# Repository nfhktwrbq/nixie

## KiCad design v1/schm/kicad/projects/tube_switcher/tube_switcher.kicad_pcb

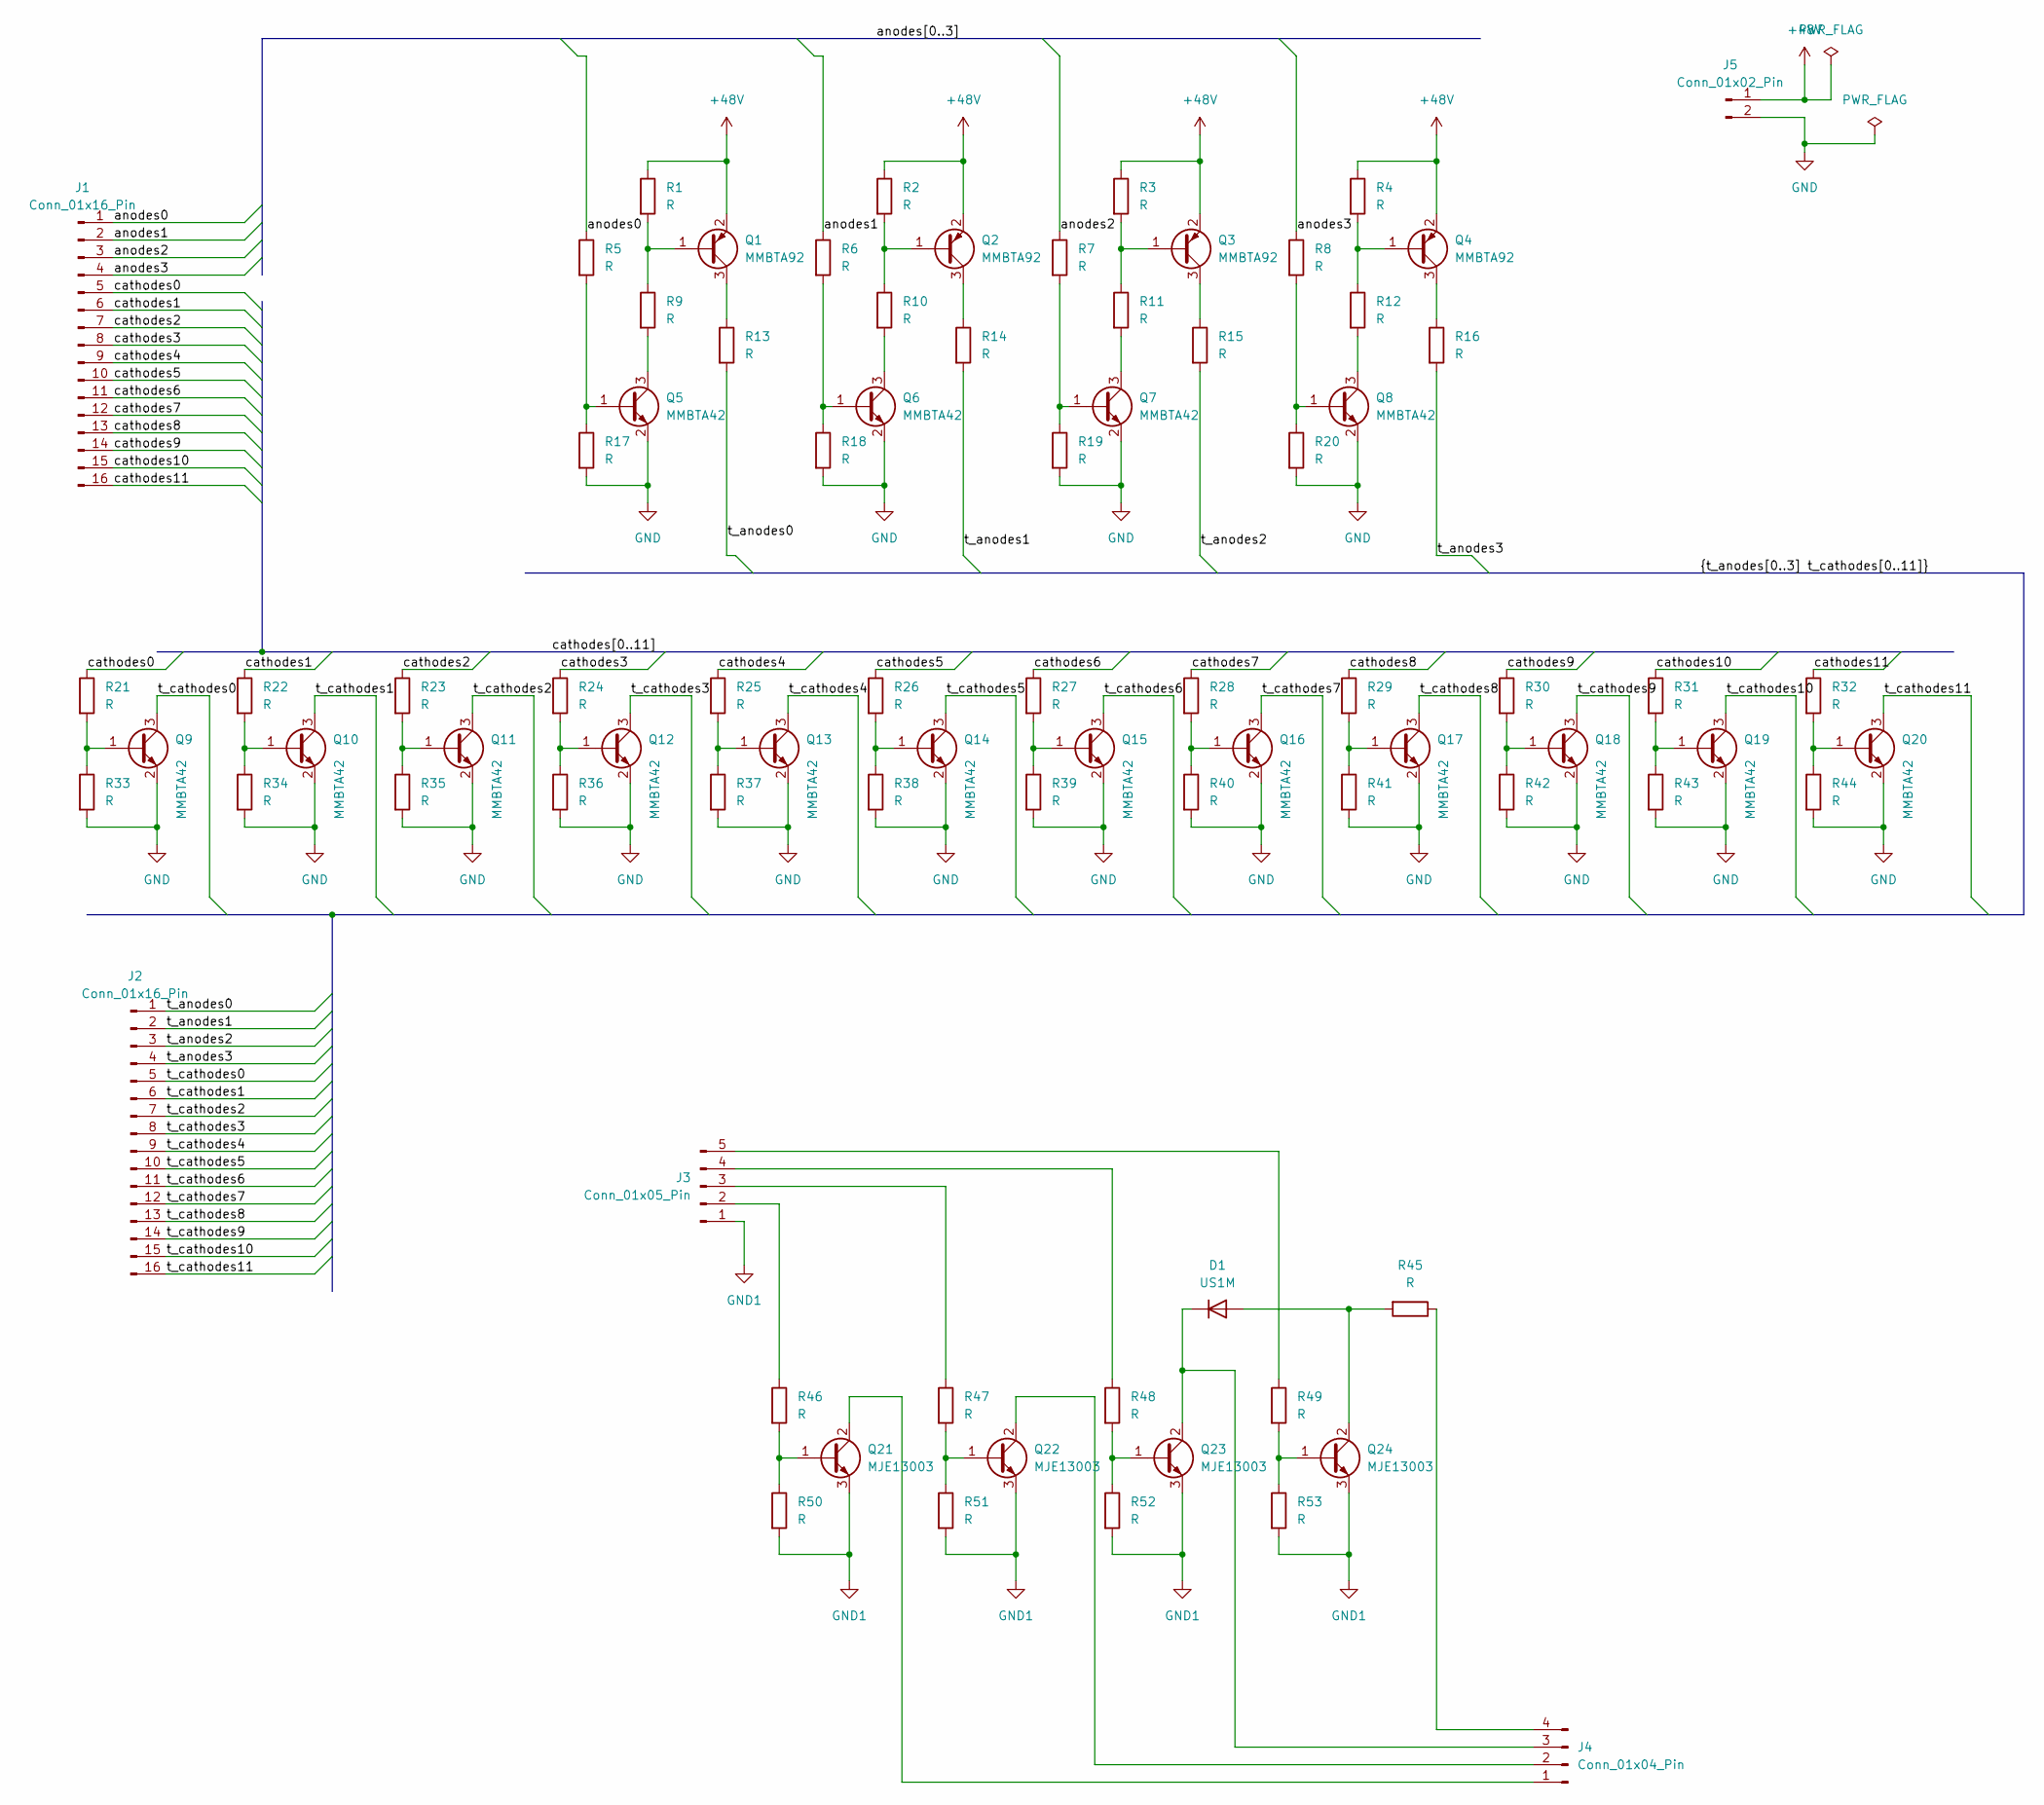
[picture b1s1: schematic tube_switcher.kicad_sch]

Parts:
D1: US1M; D_SMA
J1, J2: Conn_01x16_Pin; JST_XH_B16B-XH-A_1x16_P2.50mm_Vertical
J3: Conn_01x05_Pin; JST_XH_B5B-XH-A_1x05_P2.50mm_Vertical
J4: Conn_01x04_Pin; JST_XH_B4B-XH-A_1x04_P2.50mm_Vertical
J5: Conn_01x02_Pin; JST_XH_B2B-XH-A_1x02_P2.50mm_Vertical
Q1, Q2, Q3, Q4: MMBTA92; SOT-23
Q5, Q6, Q7, Q8, Q9, Q10, Q11, Q12, Q13, Q14, Q15, Q16, Q17, Q18, Q19, Q20: MMBTA42; SOT-23
Q21, Q22, Q23, Q24: MJE13003; TO-92_Inline_Wide
R1, R2, R3, R4, R9, R10, R11, R12: R; R_0805_2012Metric_Pad1.20x1.40mm_HandSolder
R5, R6, R7, R8, R17, R18, R19, R20, R21, R22, R23, R24, R25, R26, R27, R28, R29, R30, R31, R32, R33, R34, R35, R36, R37, R38, R39, R40, R41, R42, R43, R44, R46, R47, R48, R49, R50, R51, R52, R53: R; R_0402_1005Metric_Pad0.72x0.64mm_HandSolder
R13, R14, R15, R16, R45: R; R_1206_3216Metric_Pad1.30x1.75mm_HandSolder

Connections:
+48V: J5.1, Q1.2 (E), Q2.2 (E), Q3.2 (E), Q4.2 (E), R1.1, R2.1, R3.1, R4.1
/anodes0: J1.1, R5.1
/anodes1: J1.2, R6.1
/anodes2: J1.3, R7.1
/anodes3: J1.4, R8.1
/cathodes0: J1.5, R21.1
/cathodes1: J1.6, R22.1
/cathodes2: J1.7, R23.1
/cathodes3: J1.8, R24.1
/cathodes4: J1.9, R25.1
/cathodes5: J1.10, R26.1
/cathodes6: J1.11, R27.1
/cathodes7: J1.12, R28.1
/cathodes8: J1.13, R29.1
/cathodes9: J1.14, R30.1
/cathodes10: J1.15, R31.1
/cathodes11: J1.16, R32.1
/t_anodes0: J2.1, R13.2
/t_anodes1: J2.2, R14.2
/t_anodes2: J2.3, R15.2
/t_anodes3: J2.4, R16.2
/t_cathodes0: J2.5, Q9.3 (C)
/t_cathodes1: J2.6, Q10.3 (C)
/t_cathodes2: J2.7, Q11.3 (C)
/t_cathodes3: J2.8, Q12.3 (C)
/t_cathodes4: J2.9, Q13.3 (C)
/t_cathodes5: J2.10, Q14.3 (C)
/t_cathodes6: J2.11, Q15.3 (C)
/t_cathodes7: J2.12, Q16.3 (C)
/t_cathodes8: J2.13, Q17.3 (C)
/t_cathodes9: J2.14, Q18.3 (C)
/t_cathodes10: J2.15, Q19.3 (C)
/t_cathodes11: J2.16, Q20.3 (C)
GND: J5.2, Q5.2 (E), Q6.2 (E), Q7.2 (E), Q8.2 (E), Q9.2 (E), Q10.2 (E), Q11.2 (E), Q12.2 (E), Q13.2 (E), Q14.2 (E), Q15.2 (E), Q16.2 (E), Q17.2 (E), Q18.2 (E), Q19.2 (E), Q20.2 (E), R17.2, R18.2, R19.2, R20.2, R33.2, R34.2, R35.2, R36.2, R37.2, R38.2, R39.2, R40.2, R41.2, R42.2, R43.2, R44.2
GND1: J3.1, Q21.3 (E), Q22.3 (E), Q23.3 (E), Q24.3 (E), R50.2, R51.2, R52.2, R53.2
unnamed: D1.2 (A), Q24.2 (C), R45.2
unnamed: D1.1 (K), J4.3, Q23.2 (C)
unnamed: J3.2, R46.1
unnamed: J3.3, R47.1
unnamed: J3.4, R48.1
unnamed: J3.5, R49.1
unnamed: J4.1, Q21.2 (C)
unnamed: J4.2, Q22.2 (C)
unnamed: J4.4, R45.1
unnamed: Q1.1 (B), R1.2, R9.1
unnamed: Q1.3 (C), R13.1
unnamed: Q2.1 (B), R2.2, R10.1
unnamed: Q2.3 (C), R14.1
unnamed: Q3.1 (B), R3.2, R11.1
unnamed: Q3.3 (C), R15.1
unnamed: Q4.1 (B), R4.2, R12.1
unnamed: Q4.3 (C), R16.1
unnamed: Q5.1 (B), R5.2, R17.1
unnamed: Q5.3 (C), R9.2
unnamed: Q6.1 (B), R6.2, R18.1
unnamed: Q6.3 (C), R10.2
unnamed: Q7.1 (B), R7.2, R19.1
unnamed: Q7.3 (C), R11.2
unnamed: Q8.1 (B), R8.2, R20.1
unnamed: Q8.3 (C), R12.2
unnamed: Q9.1 (B), R21.2, R33.1
unnamed: Q10.1 (B), R22.2, R34.1
unnamed: Q11.1 (B), R23.2, R35.1
unnamed: Q12.1 (B), R24.2, R36.1
unnamed: Q13.1 (B), R25.2, R37.1
unnamed: Q14.1 (B), R26.2, R38.1
unnamed: Q15.1 (B), R27.2, R39.1
unnamed: Q16.1 (B), R28.2, R40.1
unnamed: Q17.1 (B), R29.2, R41.1
unnamed: Q18.1 (B), R30.2, R42.1
unnamed: Q19.1 (B), R31.2, R43.1
unnamed: Q20.1 (B), R32.2, R44.1
unnamed: Q21.1 (B), R46.2, R50.1
unnamed: Q22.1 (B), R47.2, R51.1
unnamed: Q23.1 (B), R48.2, R52.1
unnamed: Q24.1 (B), R49.2, R53.1

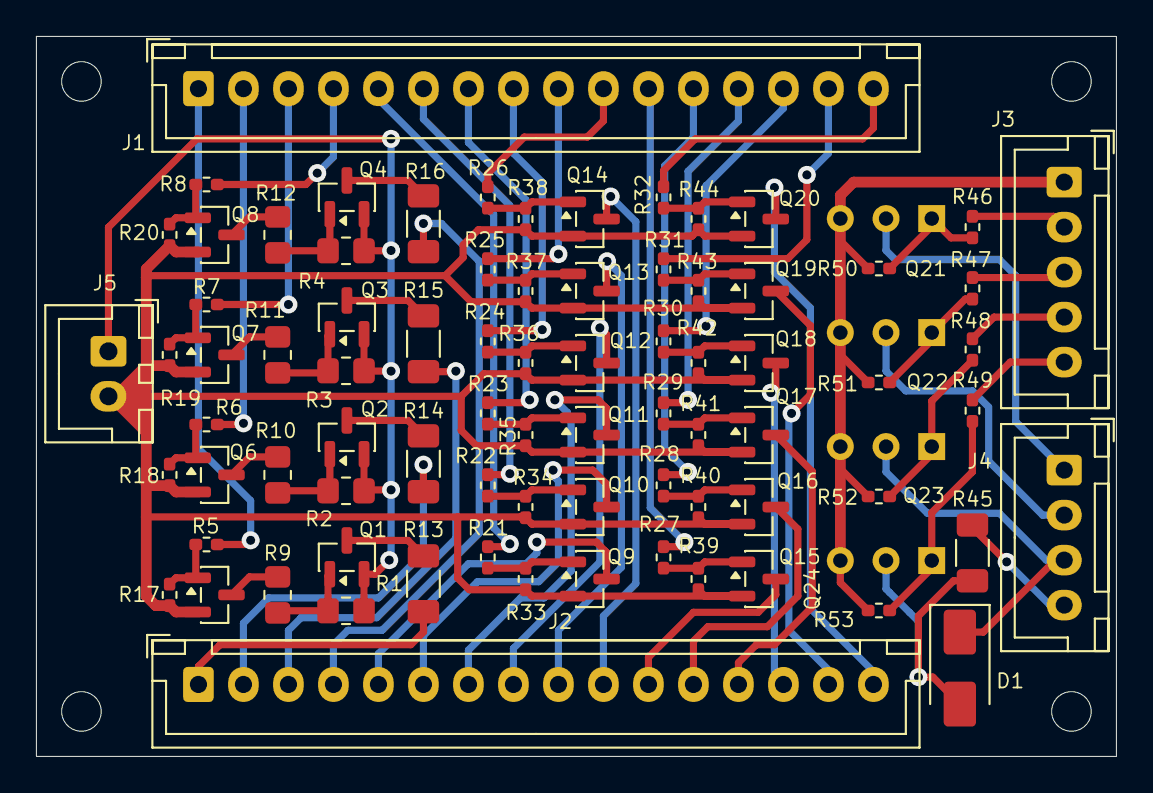
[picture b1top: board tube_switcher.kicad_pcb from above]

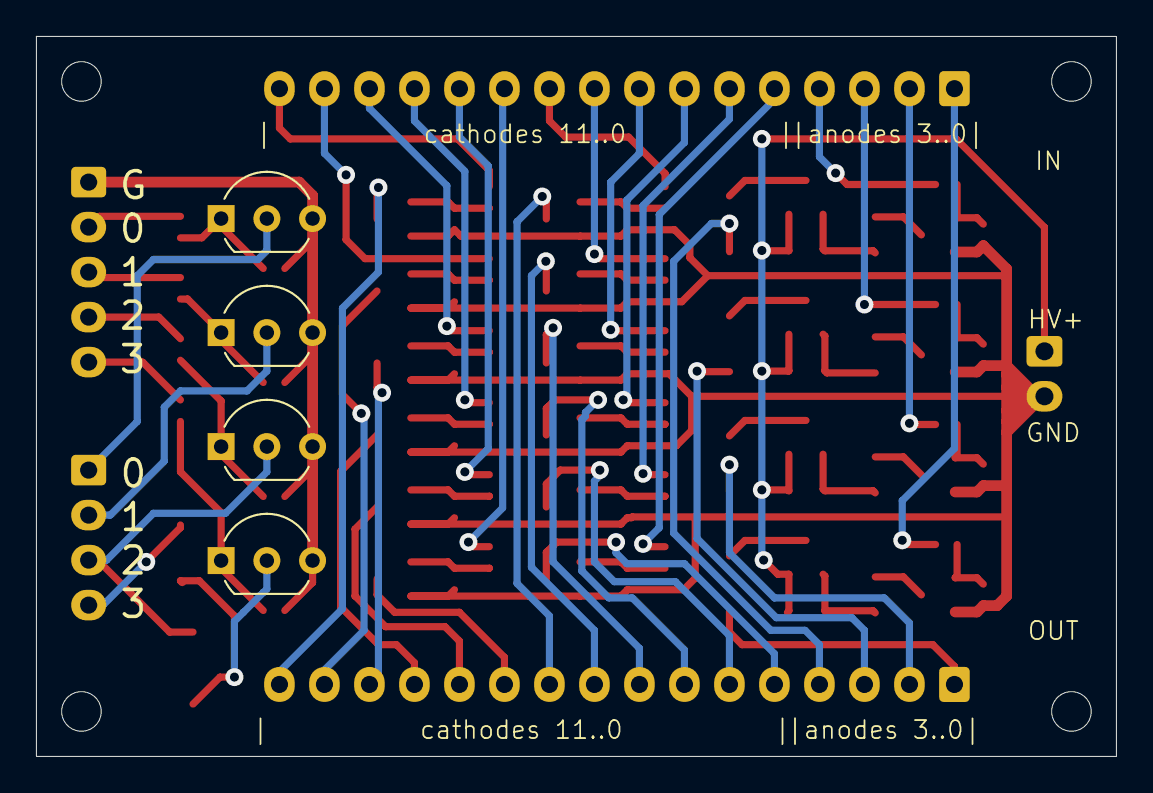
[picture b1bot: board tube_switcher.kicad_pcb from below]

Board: 2 copper layers, 60.0 x 40.0 mm, 83 parts (4 on the bottom side), 76 nets.

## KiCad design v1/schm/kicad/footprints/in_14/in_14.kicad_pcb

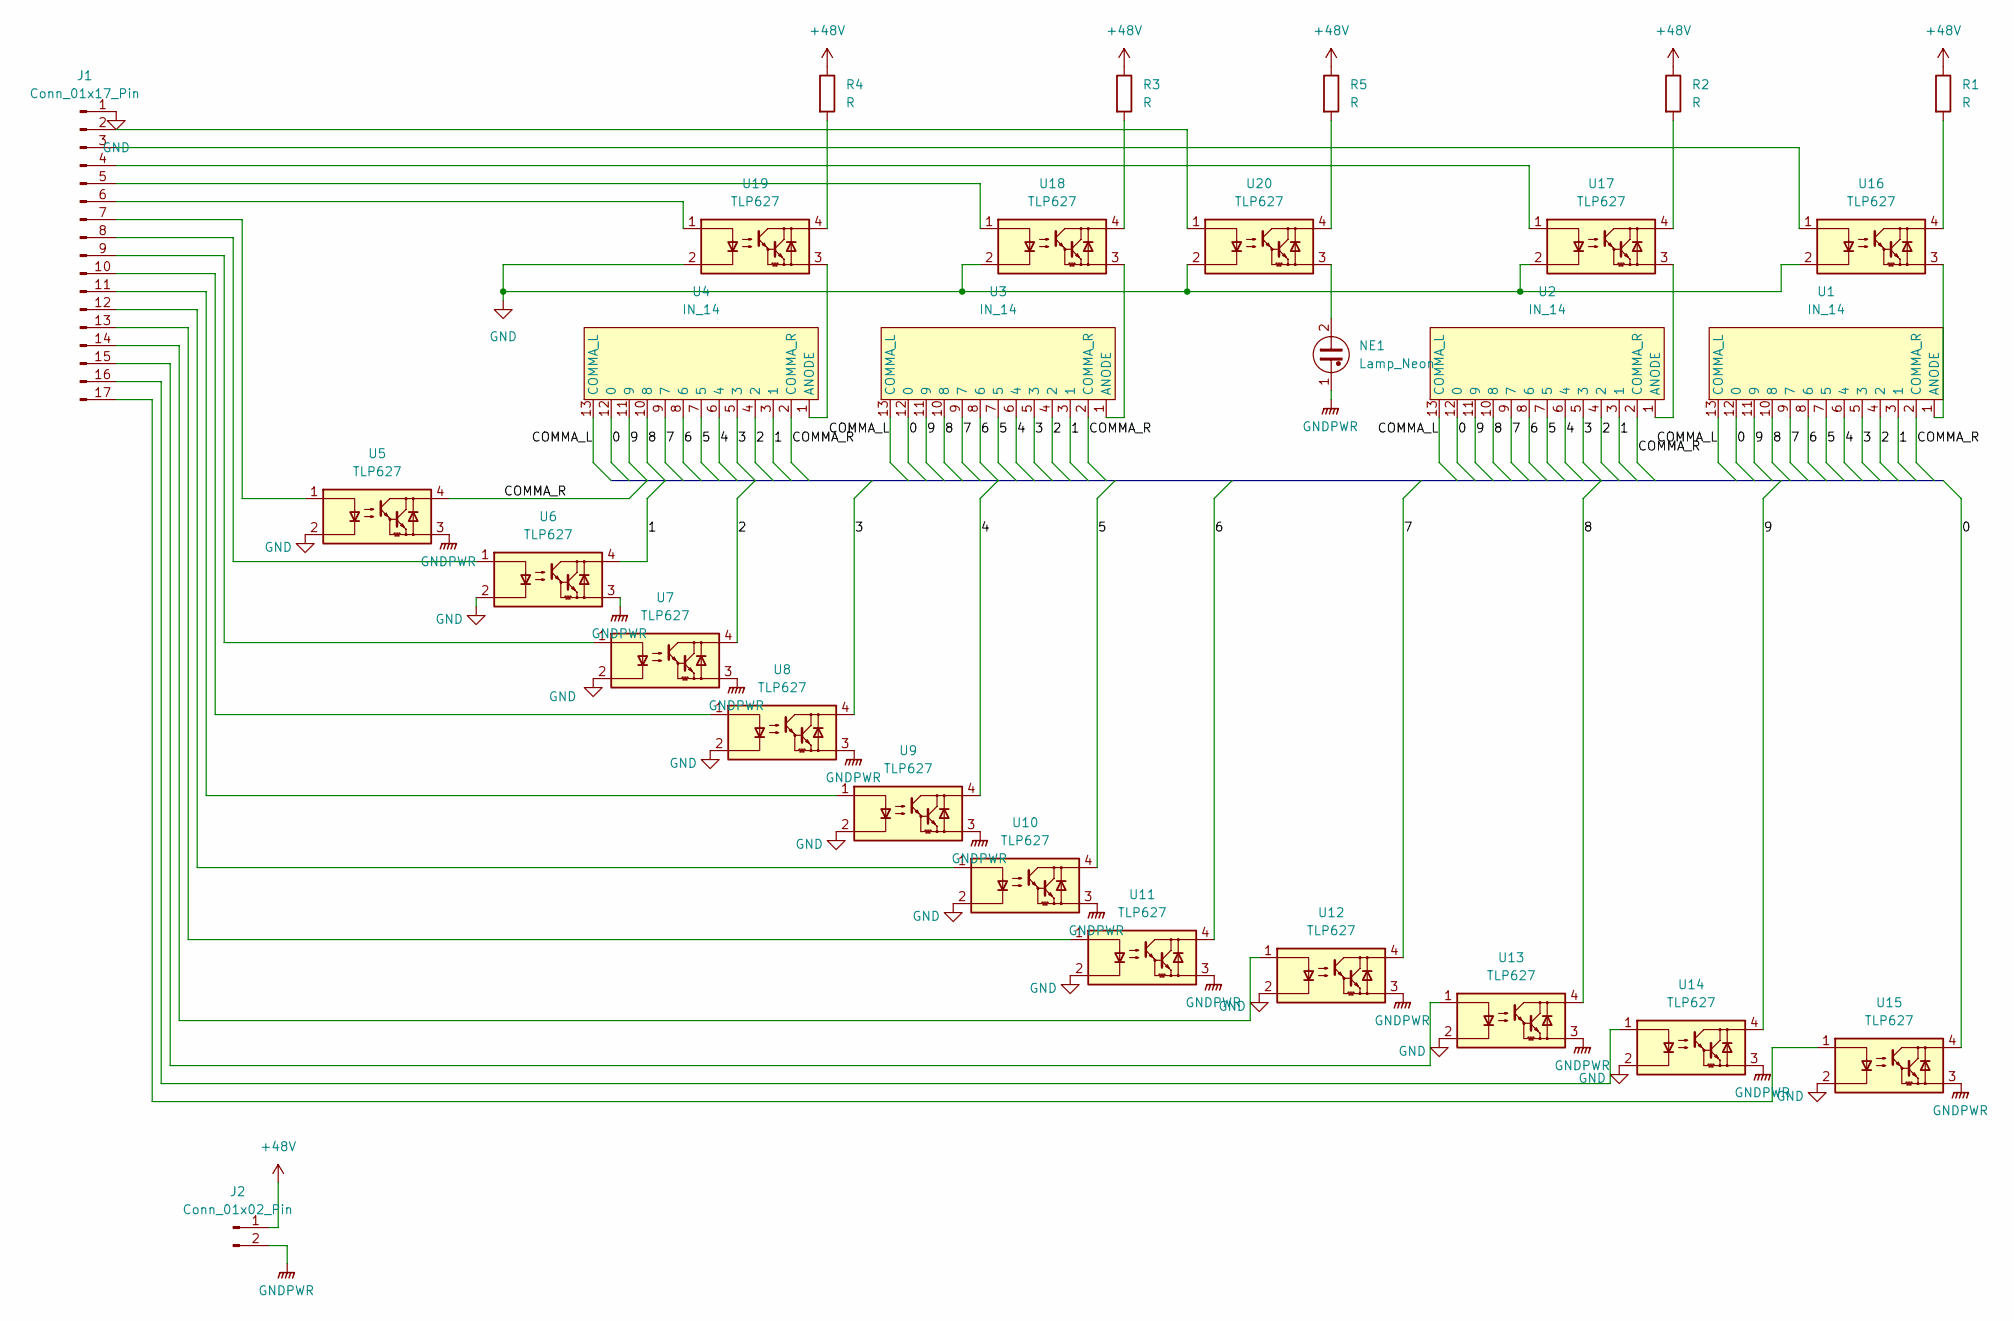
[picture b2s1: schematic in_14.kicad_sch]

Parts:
J1: Conn_01x17_Pin; PinHeader_1x17_P2.54mm_Vertical
J2: Conn_01x02_Pin; PinHeader_1x02_P2.54mm_Vertical
NE1: Lamp_Neon; LED_D5.0mm
R1, R2, R3, R4, R5: R; R_Axial_DIN0414_L11.9mm_D4.5mm_P15.24mm_Horizontal
U1, U2, U3, U4: IN_14
U5, U6, U7, U8, U9, U10, U11, U12, U13, U14, U15, U16, U17, U18, U19, U20: TLP627; DIP-4_W7.62mm

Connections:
+48V: J2.1, R1.1, R2.1, R3.1, R4.1, R5.1
/0: U1.12 (0), U2.12 (0), U3.12 (0), U4.12 (0), U15.4
/1: U1.3 (1), U2.3 (1), U3.3 (1), U4.3 (1), U6.4
/2: U1.4 (2), U2.4 (2), U3.4 (2), U4.4 (2), U7.4
/3: U1.5 (3), U2.5 (3), U3.5 (3), U4.5 (3), U8.4
/4: U1.6 (4), U2.6 (4), U3.6 (4), U4.6 (4), U9.4
/5: U1.7 (5), U2.7 (5), U3.7 (5), U4.7 (5), U10.4
/6: U1.8 (6), U2.8 (6), U3.8 (6), U4.8 (6), U11.4
/7: U1.9 (7), U2.9 (7), U3.9 (7), U4.9 (7), U12.4
/8: U1.10 (8), U2.10 (8), U3.10 (8), U4.10 (8), U13.4
/9: U1.11 (9), U2.11 (9), U3.11 (9), U4.11 (9), U14.4
/COMMA_L: U1.13 (COMMA_L), U2.13 (COMMA_L), U3.13 (COMMA_L), U4.13 (COMMA_L)
/COMMA_R: U1.2 (COMMA_R), U2.2 (COMMA_R), U3.2 (COMMA_R), U4.2 (COMMA_R), U5.4
GND: J1.1, U5.2, U6.2, U7.2, U8.2, U9.2, U10.2, U11.2, U12.2, U13.2, U14.2, U15.2, U16.2, U17.2, U18.2, U19.2, U20.2
GNDPWR: J2.2, NE1.1, U5.3, U6.3, U7.3, U8.3, U9.3, U10.3, U11.3, U12.3, U13.3, U14.3, U15.3
unnamed: J1.2, U20.1
unnamed: J1.3, U16.1
unnamed: J1.4, U17.1
unnamed: J1.5, U18.1
unnamed: J1.6, U19.1
unnamed: J1.7, U5.1
unnamed: J1.8, U6.1
unnamed: J1.9, U7.1
unnamed: J1.10, U8.1
unnamed: J1.11, U9.1
unnamed: J1.12, U10.1
unnamed: J1.13, U11.1
unnamed: J1.14, U12.1
unnamed: J1.15, U13.1
unnamed: J1.16, U14.1
unnamed: J1.17, U15.1
unnamed: NE1.2, U20.3
unnamed: R1.2, U16.4
unnamed: R2.2, U17.4
unnamed: R3.2, U18.4
unnamed: R4.2, U19.4
unnamed: R5.2, U20.4
unnamed: U1.1 (ANODE), U16.3
unnamed: U2.1 (ANODE), U17.3
unnamed: U3.1 (ANODE), U18.3
unnamed: U4.1 (ANODE), U19.3

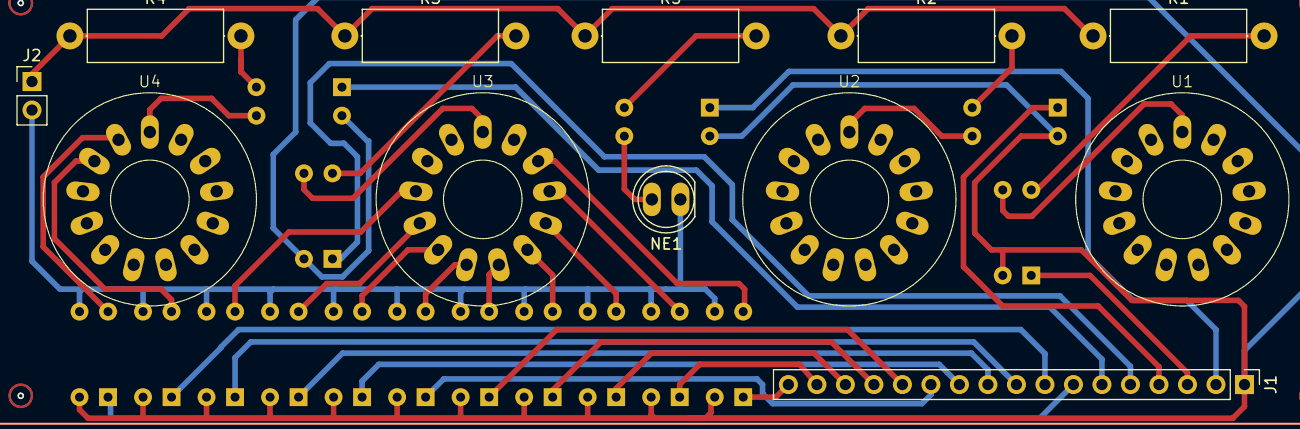
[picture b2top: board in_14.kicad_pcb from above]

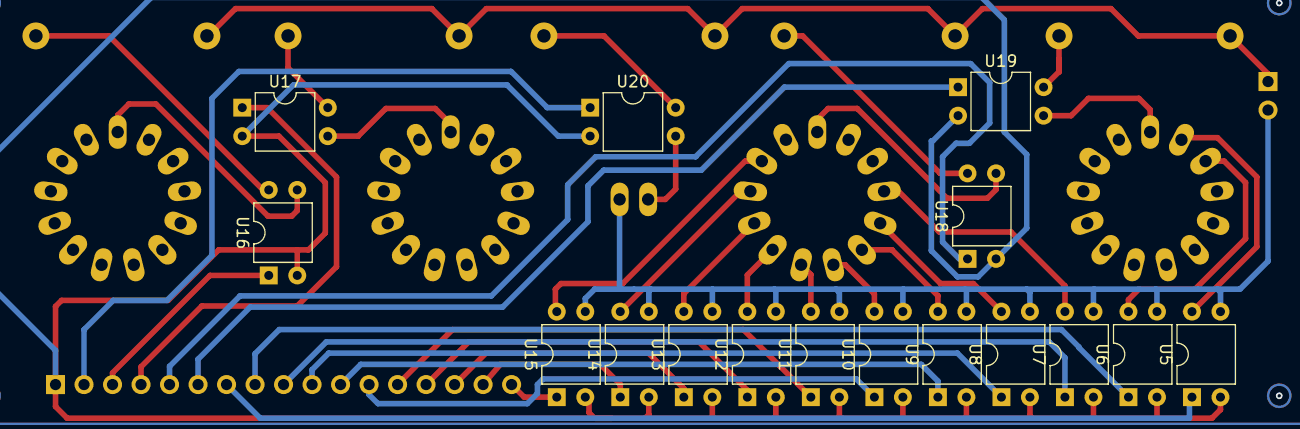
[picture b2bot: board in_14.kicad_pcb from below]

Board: 4 copper layers, 28 parts (16 on the bottom side), 41 nets.

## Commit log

2024-06-27 init commit
2024-07-07 RTC and clock init. Configs for с6 and c8
2024-07-07 schematic
2024-07-14 Edits for makefiles
2024-12-21 common makefile
2025-01-18 correct makefile tool build and other edits
2025-01-18 makefile with sizes
2025-01-20 i2c added but not tested
2025-01-26 i2c is working
2025-01-30 free_rtos is working
2025-01-30 free_rtos config
2025-02-01 simple blocking i2c is added
2025-02-01 bme280 is working. temp is checked
2025-02-01 bme is working
2025-02-02 printf module and directories reorganization
2025-02-02 directories reorganization
2025-02-02 uart reorganized and printf is working
2025-02-04 rtc, bkp, debug print
2025-11-09 refactor
2025-11-14 refactor. separate task for bme280
2025-11-23 Buttons work
2025-11-29 system frequency fixed
2025-11-29 refactor. dispaly raw added
2025-11-30 settings - store/restore. rtc irq
2026-01-01 irq i2c added and tested
2026-01-24 display edits
2026-01-24 3d body freecad parts added
2026-01-24 stl models are added
2026-02-07 i2c fix
2026-02-08 clock displayed
2026-02-08 3d files update
2026-03-09 clock setting menu
2026-03-09 tube switcher board kicad project
